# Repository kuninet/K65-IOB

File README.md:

# 6502マイコン用 I/Oボード

## 概要
- 6502マイコンやSBC68系バスへ接続可能なI/Oボードです。
  - lite版は CPUボードのクロックが1.8432MHzとなっていることを前提としています。(PHY2(E)クロックがシリアルクロックと同じ前提)
- W65C22(VIA)やW65C51(ACIA)を搭載しています

## 回路図

## パーツリスト
- パーツリストは[こちら](doc/partslist.md)。

## git branchの説明
- master
  - メインブランチ
- lite
  - 6502シングルボードコンピューター専用の軽量(手抜き)実装版

## 参考リンク
- 6502CPUシングルボードマイコン K65-SBC
  - https://github.com/kuninet/K65-SBC
- SBC-IO REV2
  - SBC68系I/Oボード。SBC68系バス改を装備しています。
  - https://sbc738827564.wordpress.com/2018/08/11/sbc-io-rev02/

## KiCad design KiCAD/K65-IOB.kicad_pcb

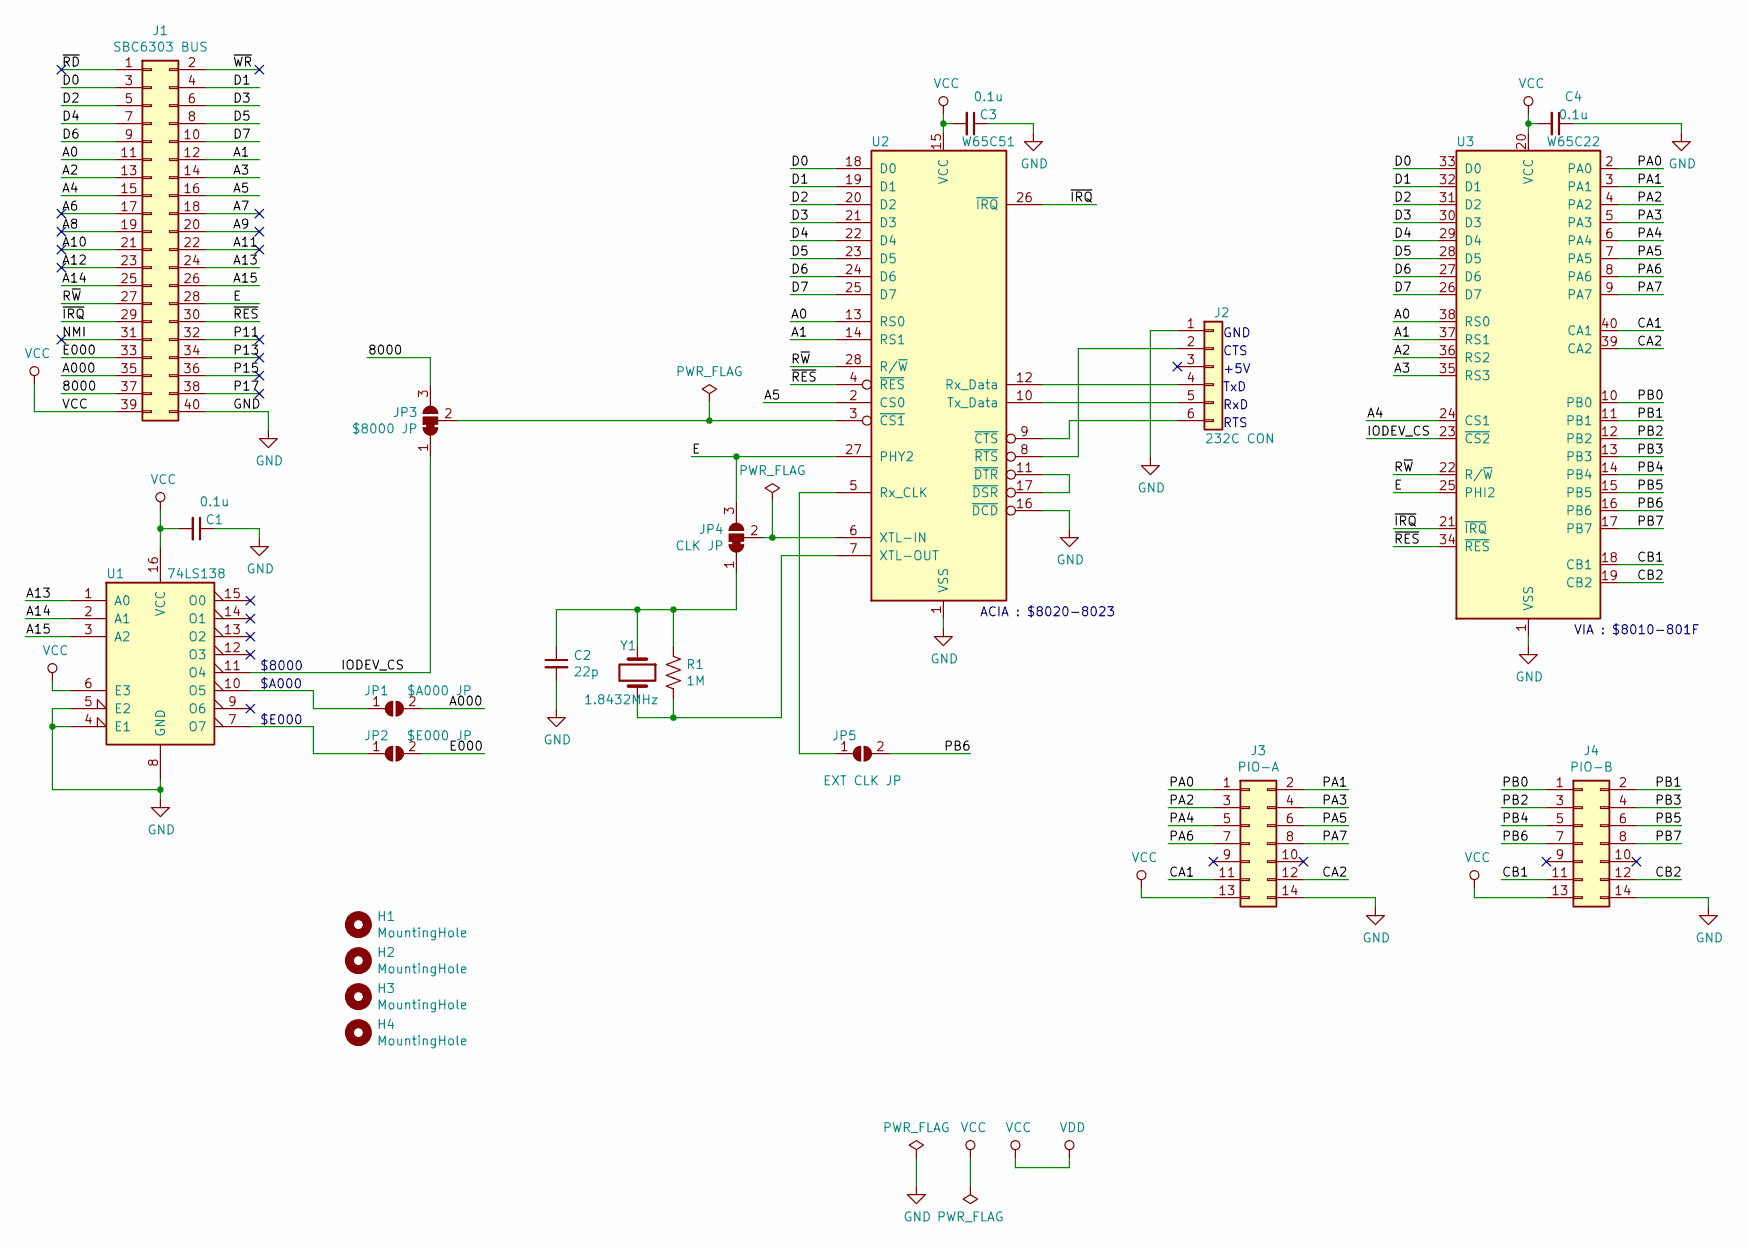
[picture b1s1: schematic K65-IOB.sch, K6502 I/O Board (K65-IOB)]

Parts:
C1, C3, C4: 0.1u; C_Disc_D3.0mm_W1.6mm_P2.50mm
C2: 22p; C_Disc_D3.0mm_W1.6mm_P2.50mm
H1, H2, H3, H4: MountingHole; MountingHole_3.2mm_M3
J1: SBC6303 BUS; PinHeader_2x20_P2.54mm_Horizontal
J2: 232C CON; PinHeader_1x06_P2.54mm_Horizontal
J3: PIO-A; PinHeader_2x07_P2.54mm_Vertical
J4: PIO-B; PinHeader_2x07_P2.54mm_Vertical
JP1: $A000 JP; SolderJumper-2_P1.3mm_Open_RoundedPad1.0x1.5mm
JP2: $E000 JP; SolderJumper-2_P1.3mm_Open_RoundedPad1.0x1.5mm
JP3: $8000 JP; SolderJumper-3_P1.3mm_Bridged12_RoundedPad1.0x1.5mm
JP4: CLK JP; SolderJumper-3_P1.3mm_Bridged12_RoundedPad1.0x1.5mm
JP5: EXT CLK JP; SolderJumper-2_P1.3mm_Open_RoundedPad1.0x1.5mm
R1: 1M; R_Axial_DIN0204_L3.6mm_D1.6mm_P7.62mm_Horizontal
U1: 74LS138; DIP-16_W7.62mm_Socket
U2: W65C51; DIP-28_W15.24mm_Socket
U3: W65C22; DIP-40_W15.24mm_Socket
Y1: 1.8432MHz; Crystal_HC49-U_Vertical

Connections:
/8000: J1.37, JP3.3 (B)
/A0: J1.11, U2.13 (RS0), U3.38 (RS0)
/A000: J1.35, JP1.2 (B)
/A1: J1.12, U2.14 (RS1), U3.37 (RS1)
/A2: J1.13, U3.36 (RS2)
/A3: J1.14, U3.35 (RS3)
/A4: J1.15, U3.24 (CS1)
/A5: J1.16, U2.2 (CS0)
/A6: J1.17
/A7: J1.18
/A8: J1.19
/A9: J1.20
/A10: J1.21
/A11: J1.22
/A12: J1.23
/A13: J1.24, U1.1 (A0)
/A14: J1.25, U1.2 (A1)
/A15: J1.26, U1.3 (A2)
/CA1: J3.11, U3.40 (CA1)
/CA2: J3.12, U3.39 (CA2)
/CB1: J4.11, U3.18 (CB1)
/CB2: J4.12, U3.19 (CB2)
/D0: J1.3, U2.18 (D0), U3.33 (D0)
/D1: J1.4, U2.19 (D1), U3.32 (D1)
/D2: J1.5, U2.20 (D2), U3.31 (D2)
/D3: J1.6, U2.21 (D3), U3.30 (D3)
/D4: J1.7, U2.22 (D4), U3.29 (D4)
/D5: J1.8, U2.23 (D5), U3.28 (D5)
/D6: J1.9, U2.24 (D6), U3.27 (D6)
/D7: J1.10, U2.25 (D7), U3.26 (D7)
/E: J1.28, JP4.3 (B), U2.27 (PHY2), U3.25 (PHI2)
/E000: J1.33, JP2.2 (B)
/IODEV_CS: JP3.1 (A), U1.11 (O4), U3.23 (~CS2)
/NMI: J1.31
/P11: J1.32
/P13: J1.34
/P15: J1.36
/P17: J1.38
/PA0: J3.1, U3.2 (PA0)
/PA1: J3.2, U3.3 (PA1)
/PA2: J3.3, U3.4 (PA2)
/PA3: J3.4, U3.5 (PA3)
/PA4: J3.5, U3.6 (PA4)
/PA5: J3.6, U3.7 (PA5)
/PA6: J3.7, U3.8 (PA6)
/PA7: J3.8, U3.9 (PA7)
/PB0: J4.1, U3.10 (PB0)
/PB1: J4.2, U3.11 (PB1)
/PB2: J4.3, U3.12 (PB2)
/PB3: J4.4, U3.13 (PB3)
/PB4: J4.5, U3.14 (PB4)
/PB5: J4.6, U3.15 (PB5)
/PB6: J4.7, JP5.2 (B), U3.16 (PB6)
/PB7: J4.8, U3.17 (PB7)
/R~W: J1.27, U2.28 (R/~W), U3.22 (R/~W)
/~IRQ: J1.29, U2.26 (~IRQ), U3.21 (~IRQ)
/~RD: J1.1
/~RES: J1.30, U2.4 (~RES), U3.34 (~RES)
/~WR: J1.2
GND: C1.1, C2.2, C3.1, C4.1, J1.40, J2.1, J3.14, J4.14, U1.4 (E1), U1.5 (E2), U1.8 (GND), U2.1 (VSS), U2.16 (~DCD), U3.1 (VSS)
unnamed: C2.1, JP4.1 (A), R1.1, Y1.1
unnamed: J2.2, U2.8 (~RTS)
unnamed: J2.4, U2.12 (Rx_Data)
unnamed: J2.5, U2.10 (Tx_Data)
unnamed: J2.6, U2.9 (~CTS)
unnamed: JP1.1 (A), U1.10 (O5)
unnamed: JP2.1 (A), U1.7 (O7)
unnamed: JP3.2 (C), U2.3 (~CS1)
unnamed: JP4.2 (C), U2.6 (XTL-IN)
unnamed: JP5.1 (A), U2.5 (Rx_CLK)
unnamed: R1.2, U2.7 (XTL-OUT), Y1.2
unnamed: U2.11 (~DTR), U2.17 (~DSR)
VCC: C1.2, C3.2, C4.2, J1.39, J3.13, J4.13, U1.6 (E3), U1.16 (VCC), U2.15 (VCC), U3.20 (VCC)

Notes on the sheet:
GND
CTS
+5V
TxD
RxD
RTS
$8000
$A000
$E000
ACIA : $8020-8023
VIA : $8010-801F

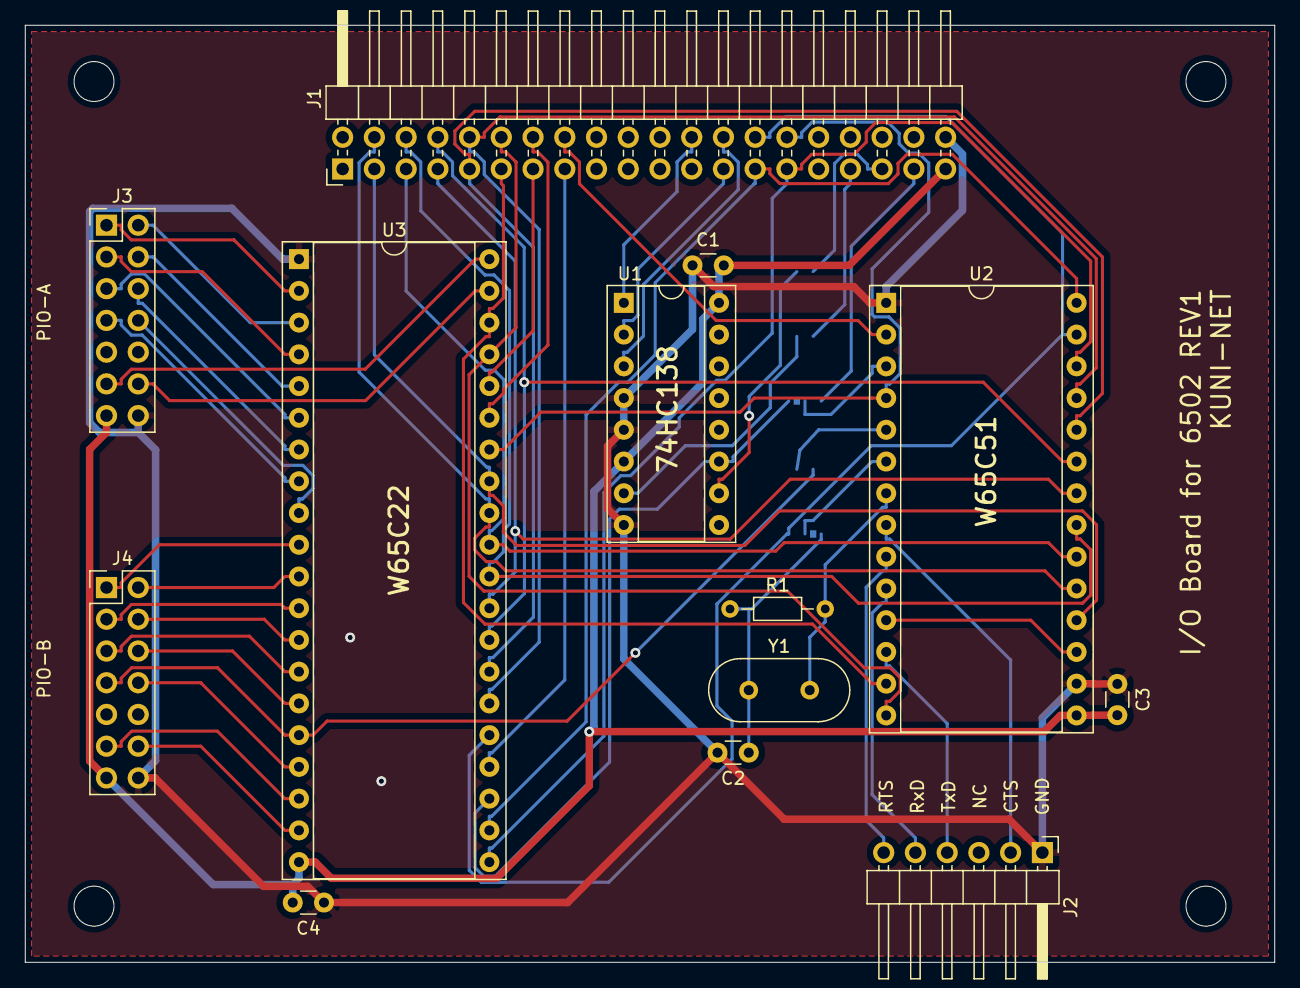
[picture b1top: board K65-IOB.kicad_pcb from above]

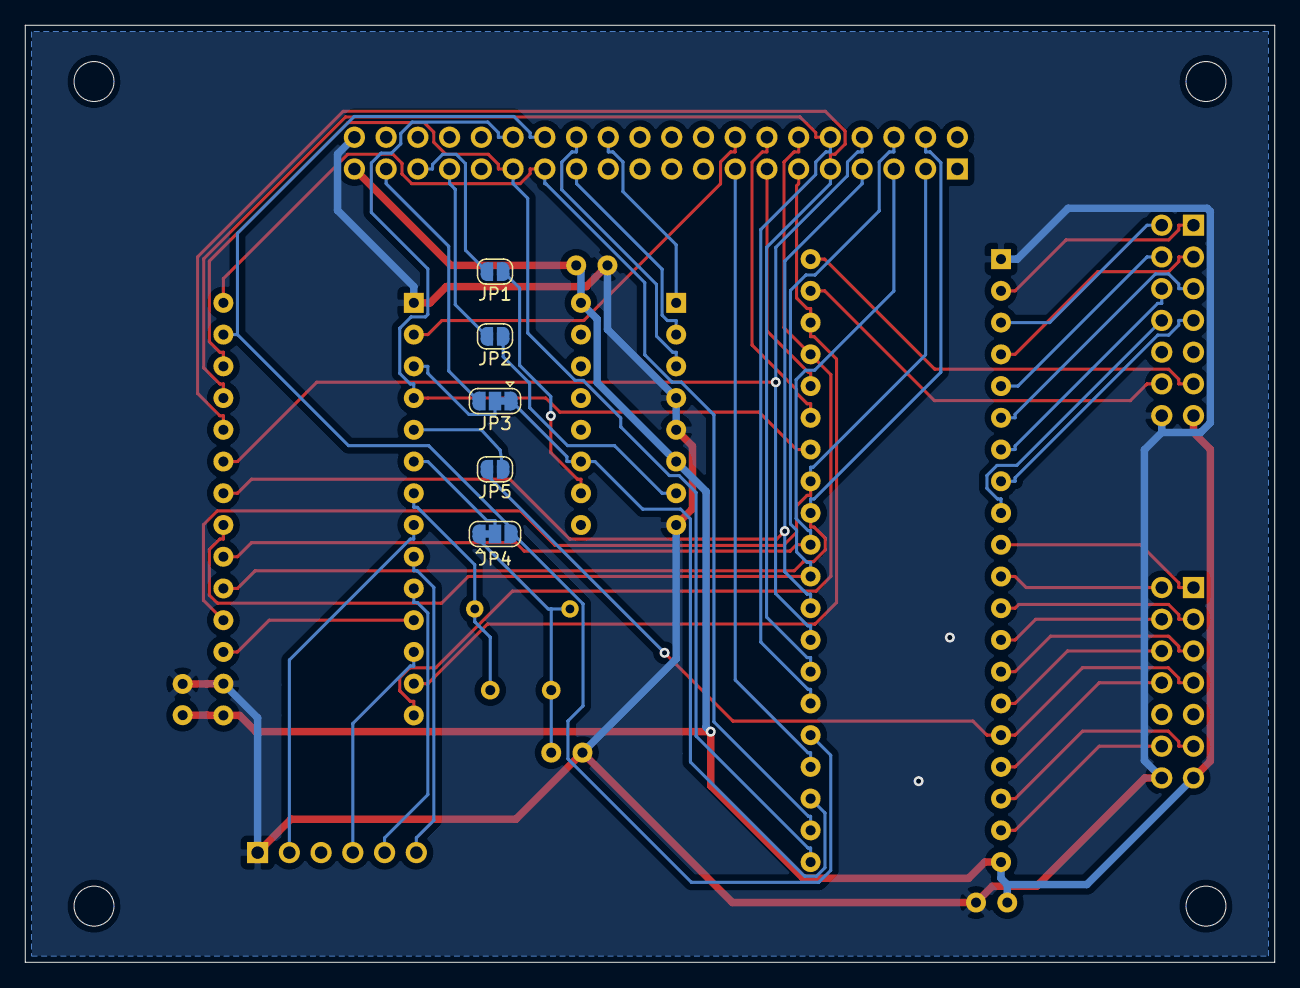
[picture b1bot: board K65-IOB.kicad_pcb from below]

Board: 2 copper layers, 100.0 x 75.0 mm, 22 parts (5 on the bottom side), 59 nets.

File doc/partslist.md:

# 部品リスト

|部品番号|仕様|数量|備考|
|:---:|:---|---:|:---|
|U1|74LS138|1|74HCT138でも可|
|U2|W65C51|1|ACIA シリアルIC|
|U3|W65C22|1|VIA 多用途I/O|
|C1,C3,C4|0.1uF|3|積層セラミックコンデンサ(バイパスコンデンサ)|
|C2|22pF or 33pF|1|積層セラミックコンデンサ、シリアル用クリスタルをつける場合|
|J1|2x20(40ピン) L型ボックスヘッダ|1|2列 L型ピンヘッダでも可|
|J2|2x2ピンヘッダ|1||
|J3|1x6 L型ピンヘッダ|1||
|J4、J5|2x7(14ピン)ボックスヘッダ|1|2列垂直ピンヘッダでも可|
||16ピン ICソケット|1||
||28ピン ICソケット|1||
||40ピン ICソケット|1||
|R1|1M|1|カーボン抵抗器シリアル用クリスタルを付ける場合|
|Y1|1.8432MHz|1|シリアル用クリスタルを付ける場合|

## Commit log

2020-06-08 init commit
2020-06-08 README作成
2020-06-08 README修正
2020-06-08 アドレスデコーダーを簡易版へ
2020-06-08 シンボル間違い等修正
2020-06-11 VIA/ACIAアドレス表示追加
2020-06-13 回路間違い修正、回路図イメージ出力
2020-06-21 Lite版をMasterへ統合、UniversalMonitor W65C51対応点添付
2020-06-21 パーツリスト追加、クリスタル周波数明示
2020-06-21 回路図 クリスタル周波数明示
2020-09-22 回路見直し、ガーバーデータ出力
2020-09-22 プリントパターン変更
